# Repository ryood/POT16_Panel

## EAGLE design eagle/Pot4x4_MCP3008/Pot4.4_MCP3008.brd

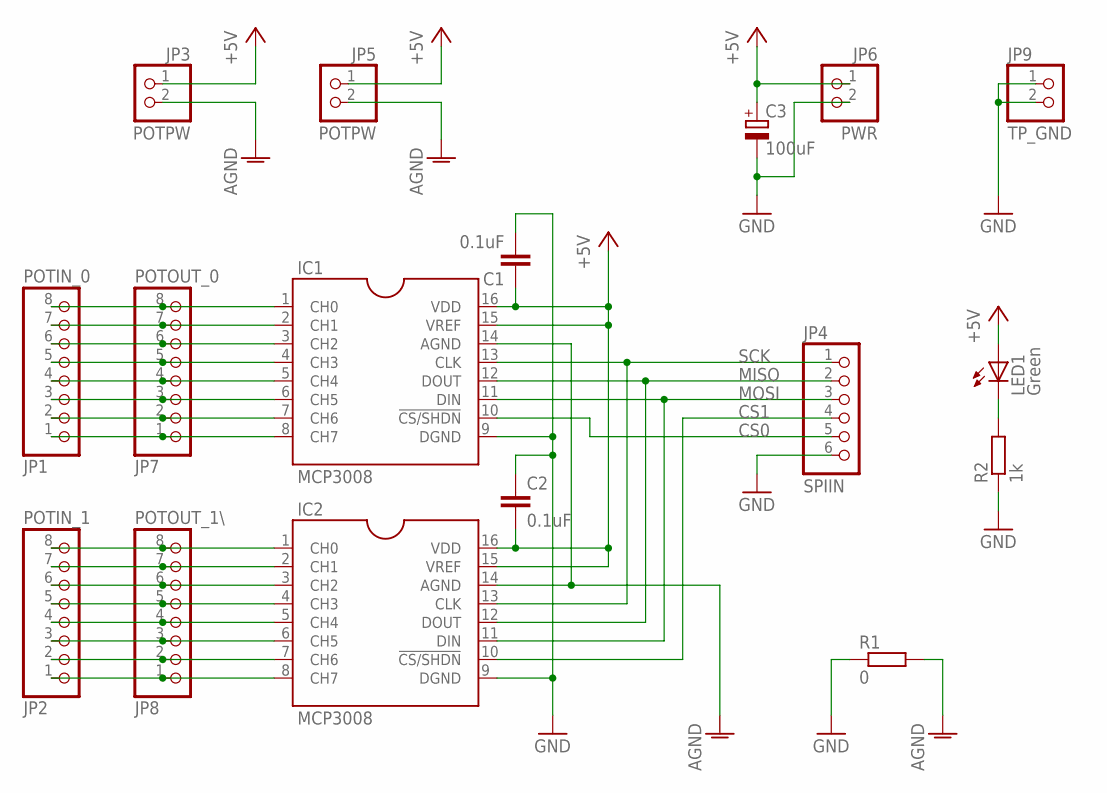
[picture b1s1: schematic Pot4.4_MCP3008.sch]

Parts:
C1, C2: 0.1uF; C025-024X044
C3: 100uF; SANYO-OSCON_C
IC1, IC2: MCP3008
JP1: POTIN_0; 1X08/90
JP2: POTIN_1; 1X08/90
JP3, JP5: POTPW; 1X02/90
JP4: SPIIN; 1X06/90
JP6: PWR; 1X02/90
JP7: POTOUT_0; 1X08
JP8: POTOUT_1\; 1X08
JP9: TP_GND; 1X02
LED1: Green; LED3MM
R1: 0; 0204V
R2: 1k; 0207/7

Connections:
+5V: C1.1, C2.2, C3.+, IC1.15 (VREF), IC1.16 (VDD), IC2.15 (VREF), IC2.16 (VDD), JP3.1, JP5.1, JP6.1, LED1.A
AGND: IC1.14 (AGND), IC2.14 (AGND), JP3.2, JP5.2, R1.2
CS0: IC1.10 (!CS/SHDN), JP4.5
CS1: IC2.10 (!CS/SHDN), JP4.4
GND: C1.2, C2.1, C3.-, IC1.9 (DGND), IC2.9 (DGND), JP4.6, JP6.2, JP9.1, JP9.2, R1.1, R2.1
MISO: IC1.12 (DOUT), IC2.12 (DOUT), JP4.2
MOSI: IC1.11 (DIN), IC2.11 (DIN), JP4.3
unnamed: IC1.1 (CH0), JP1.8, JP7.8
unnamed: IC1.2 (CH1), JP1.7, JP7.7
unnamed: IC1.3 (CH2), JP1.6, JP7.6
unnamed: IC1.4 (CH3), JP1.5, JP7.5
unnamed: IC1.5 (CH4), JP1.4, JP7.4
unnamed: IC1.6 (CH5), JP1.3, JP7.3
unnamed: IC1.7 (CH6), JP1.2, JP7.2
unnamed: IC1.8 (CH7), JP1.1, JP7.1
unnamed: IC2.1 (CH0), JP2.8, JP8.8
unnamed: IC2.2 (CH1), JP2.7, JP8.7
unnamed: IC2.3 (CH2), JP2.6, JP8.6
unnamed: IC2.4 (CH3), JP2.5, JP8.5
unnamed: IC2.5 (CH4), JP2.4, JP8.4
unnamed: IC2.6 (CH5), JP2.3, JP8.3
unnamed: IC2.7 (CH6), JP2.2, JP8.2
unnamed: IC2.8 (CH7), JP2.1, JP8.1
unnamed: LED1.K (C), R2.2
SCK: IC1.13 (CLK), IC2.13 (CLK), JP4.1

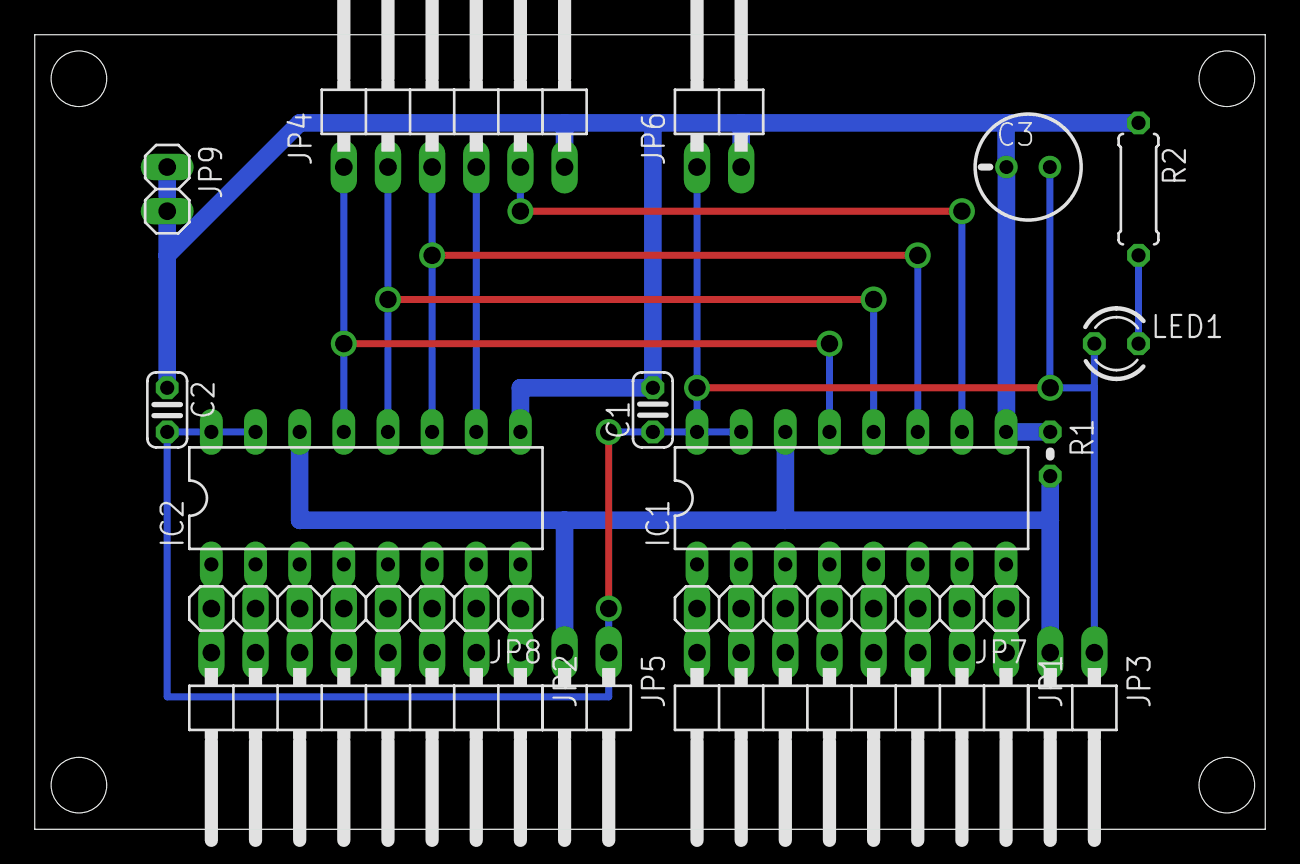
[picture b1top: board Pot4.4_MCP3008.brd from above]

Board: 2 copper layers, 70.8 x 45.7 mm, 17 parts (0 on the bottom side), 25 nets.

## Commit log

2017-06-20 Add: a Test Chart, Pictures
2017-06-21 Add: drawing of wood frame
2017-07-03 Updated: chassis
